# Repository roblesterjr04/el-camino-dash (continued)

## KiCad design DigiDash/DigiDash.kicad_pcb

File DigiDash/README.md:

# DigiDash main board, rev 1 (superseded)

**Status: superseded by [`DigiDash2/`](../DigiDash2/README.md).** Kept as the reference that rev 2 was planned from
([`docs/hardware/digidash_rev2_plan.md`](../docs/hardware/digidash_rev2_plan.md), "What rev 1 does badly"). Not on the
panel. Whether it was ever ordered or built: not stated.

**Firmware:** the on-board sensor pack runs [`arduino/sketches/sensor_pack`](../arduino/sketches/sensor_pack/); the
screens run [`firmware/esp32_p4_display`](../firmware/esp32_p4_display/).

The first main board: 309.2 × 103.7 mm, 2 layers, every part through-hole. On it:
- the three screen headers (2×20) for the Waveshare ESP32-P4 round displays, with an MCP2562 CAN transceiver per screen
- an **ATmega328P** (DIP-28) sensor pack whose serial output fans out to the three screens
  ([`docs/protocols/sensor_uart.md`](../docs/protocols/sensor_uart.md))
- plug-in modules: an FRAM board for the odometer and a TVP5150 video decoder board for the reversing camera
- an LM2576 5 V switching regulator
- four 2×5 accessory ports (J18–J21) and cable ports on the CAN bus
  ([`docs/hardware/accessory_ports.md`](../docs/hardware/accessory_ports.md), rev 1 sections)

| File | What |
| --- | --- |
| `DigiDash.kicad_sch` / `.kicad_pcb` / `.kicad_pro` | The board. There is no `generate/` folder; it was autorouted with Freerouting 2.1 (git history) |
| `DigiDash_Accessory.pretty` | The 2×5 accessory port and carrier header footprints. **Still in use:** DigiDash2, DigiDash3 and AudioCarrier list this library in their `fp-lib-table`, so keep the folder |
| `freerouting.dsn` | The Specctra export from the last autoroute |

The schematic uses symbols from KiCad's PCM SparkFun libraries (power symbols, a capacitor, a crystal) and an
`RCJ-022` symbol that is not in KiCad's stock libraries. Install those to open it without missing-symbol warnings.

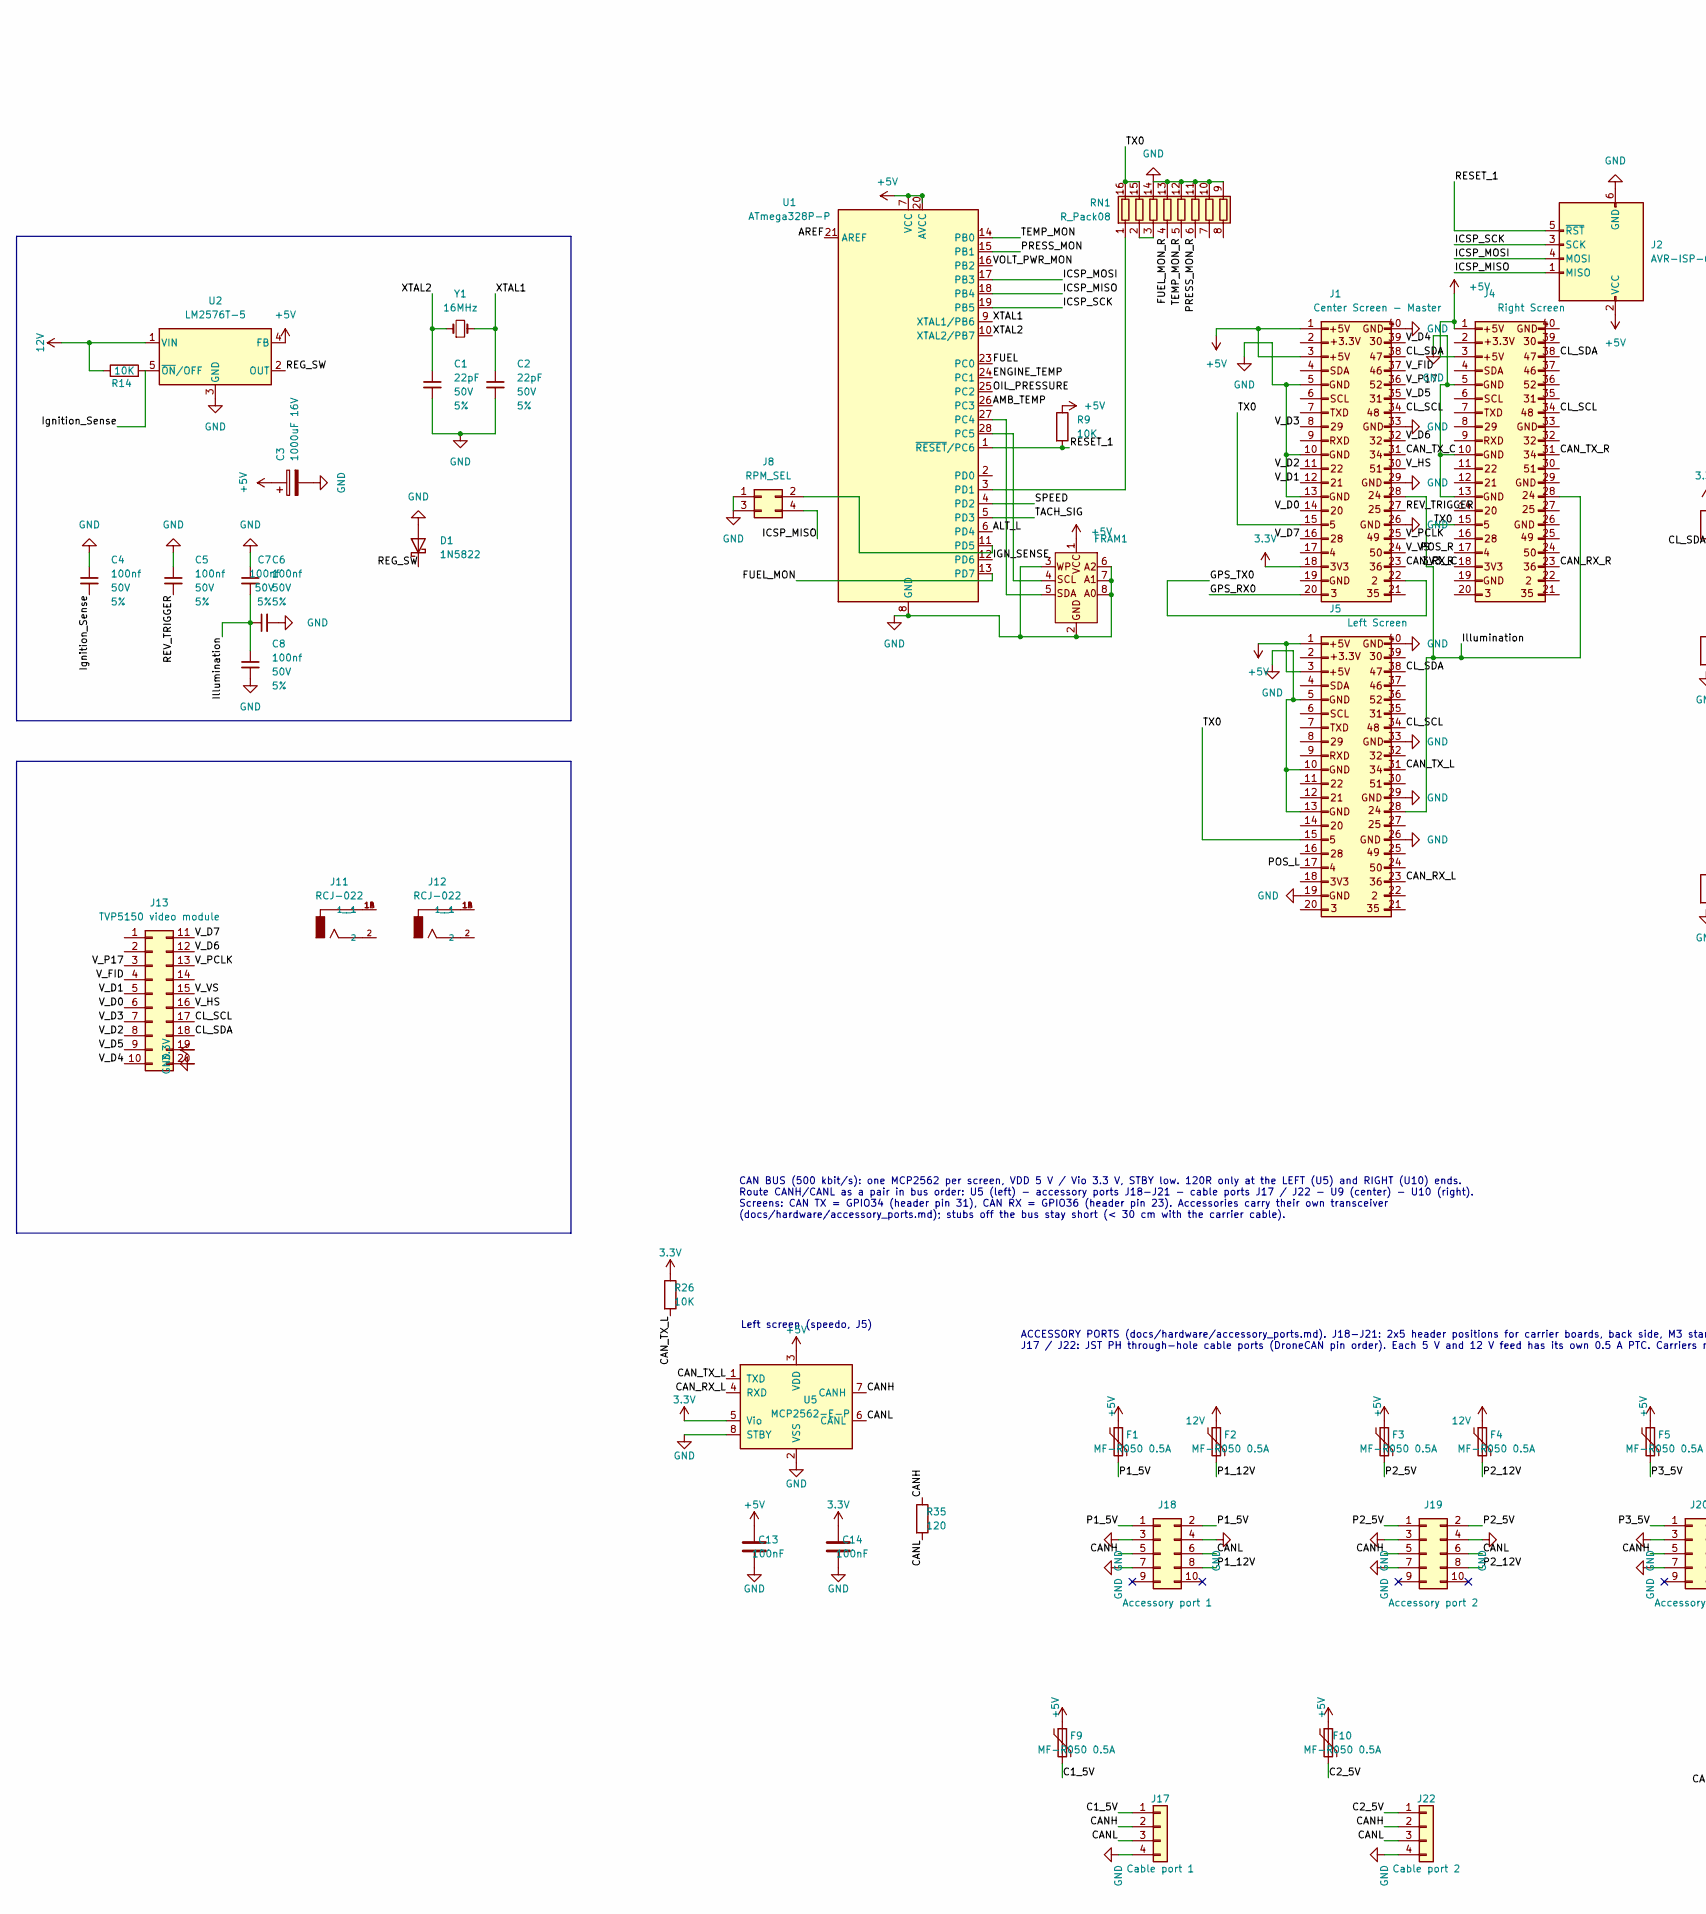
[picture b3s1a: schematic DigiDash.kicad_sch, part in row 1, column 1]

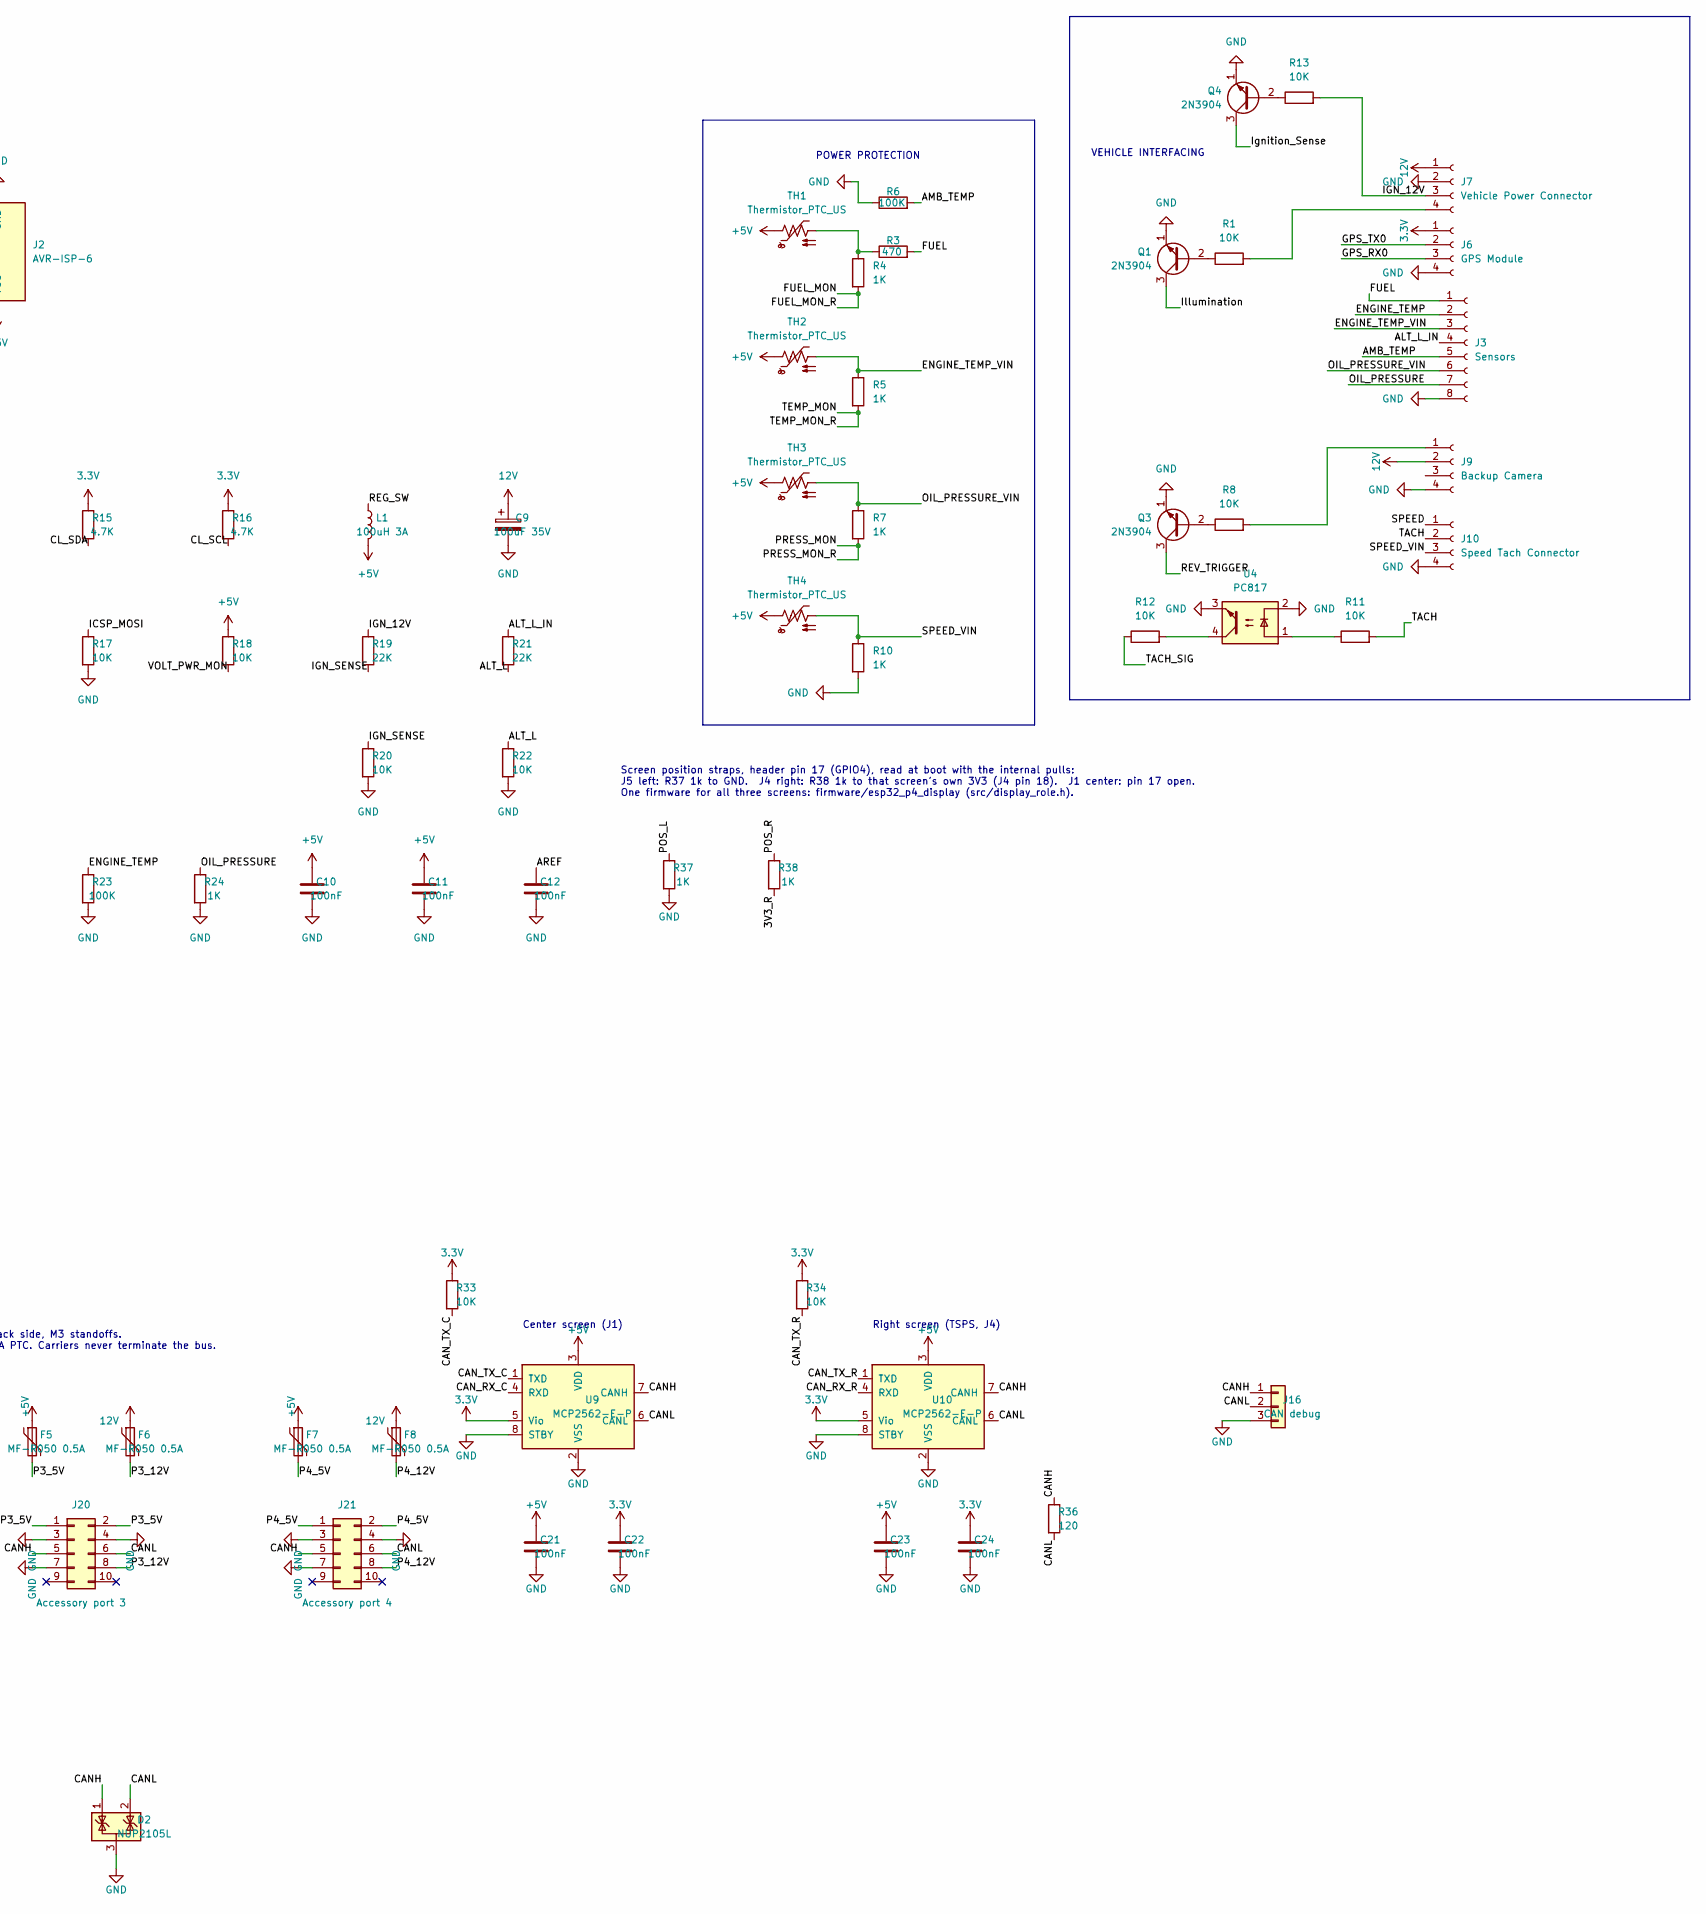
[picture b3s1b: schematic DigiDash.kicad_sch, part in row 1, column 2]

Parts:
C1, C2: 22pF; C_Disc_D3.0mm_W1.6mm_P2.50mm; Voltage 50V; Tolerance 5%
C3: 1000uF 16V; CP_Radial_D10.0mm_P5.00mm
C4, C5, C6, C7, C8: 100nf; C_Disc_D3.0mm_W1.6mm_P2.50mm; Voltage 50V; Tolerance 5%
C9: 100uF 35V; CP_Radial_D6.3mm_P2.50mm
C10, C11, C12, C13, C14, C21, C22, C23, C24: 100nF; C_Disc_D3.0mm_W1.6mm_P2.50mm
D1: 1N5822; D_DO-201AD_P15.24mm_Horizontal
D2: NUP2105L; SOT-23
F1, F2, F3, F4, F5, F6, F7, F8, F9, F10: MF-R050 0.5A; Fuse_Bourns_MF-RHT050
FRAM1: FRAM Board; PinHeader_1x08_P2.54mm_Vertical
J1: Center Screen - Master; PinHeader_2x20_P2.54mm_Vertical
J2: AVR-ISP-6; IDC-Header_2x03_P2.54mm_Vertical
J3: Sensors; JST_PH_S8B-PH-K_1x08_P2.00mm_Horizontal
J4: Right Screen; PinHeader_2x20_P2.54mm_Vertical
J5: Left Screen; PinHeader_2x20_P2.54mm_Vertical
J6: GPS Module; JST_PH_S4B-PH-K_1x04_P2.00mm_Horizontal
J7: Vehicle Power Connector; JST_PH_S4B-PH-K_1x04_P2.00mm_Horizontal
J8: RPM_SEL; PinHeader_2x02_P2.54mm_Vertical
J9: Backup Camera; JST_PH_S4B-PH-K_1x04_P2.00mm_Horizontal
J10: Speed Tach Connector; JST_PH_S4B-PH-K_1x04_P2.00mm_Horizontal
J11, J12: RCJ-022; CUI_RCJ-022; PART_REV B
J13: TVP5150 video module; PinSocket_2x10_P2.54mm_Vertical
J16: CAN debug; PinHeader_1x03_P2.54mm_Vertical
J17: Cable port 1; JST_PH_S4B-PH-K_1x04_P2.00mm_Horizontal
J18: Accessory port 1; Port_Header_2x05
J19: Accessory port 2; Port_Header_2x05
J20: Accessory port 3; Port_Header_2x05
J21: Accessory port 4; Port_Header_2x05
J22: Cable port 2; JST_PH_S4B-PH-K_1x04_P2.00mm_Horizontal
L1: 100uH 3A; L_Radial_D12.0mm_P10.00mm_Neosid_SD12_style1
Q1, Q3, Q4: 2N3904; TO-92_Inline
R1, R8, R9, R11, R12, R13, R14, R17, R18, R20, R22, R26, R33, R34: 10K; R_Axial_DIN0204_L3.6mm_D1.6mm_P5.08mm_Horizontal
R3: 470; R_Axial_DIN0204_L3.6mm_D1.6mm_P5.08mm_Horizontal
R4, R5, R7, R10, R24, R37, R38: 1K; R_Axial_DIN0204_L3.6mm_D1.6mm_P5.08mm_Horizontal
R6, R23: 100K; R_Axial_DIN0204_L3.6mm_D1.6mm_P5.08mm_Horizontal
R15, R16: 4.7K; R_Axial_DIN0204_L3.6mm_D1.6mm_P5.08mm_Horizontal
R19, R21: 22K; R_Axial_DIN0204_L3.6mm_D1.6mm_P5.08mm_Horizontal
R35, R36: 120; R_Axial_DIN0204_L3.6mm_D1.6mm_P5.08mm_Horizontal
RN1: R_Pack08; DIP-16_W7.62mm
TH1, TH2, TH3, TH4: Thermistor_PTC_US; R_Axial_DIN0516_L15.5mm_D5.0mm_P5.08mm_Vertical
U1: ATmega328P-P; DIP-28_W7.62mm
U2: LM2576T-5; TO-220-5_Vertical
U4: PC817; DIP-4_W7.62mm
U5, U9, U10: MCP2562-E-P; DIP-8_W7.62mm
Y1: 16MHz; Crystal_HC52-U_Vertical

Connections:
3.3V: C14.1, C22.1, C24.1, J1.18, J6.1, J13.19, R15.1, R16.1, R26.1, R33.1, R34.1, U5.5 (Vio), U9.5 (Vio), U10.5 (Vio)
12V: C9.1, F2.1, F4.1, F6.1, F8.1, J7.1, J9.2, R14.1, U2.1 (VIN)
+5V: C3.1, C10.1, C11.1, C13.1, C21.1, C23.1, F1.1, F3.1, F5.1, F7.1, F9.1, F10.1, FRAM1.1 (VCC), J1.1 (+5V), J1.3, J2.2 (VCC), J4.1 (+5V), J4.3, J5.1 (+5V), J5.3, L1.2, R9.1, R18.1, TH1.1, TH2.1, TH3.1, TH4.1, U1.7 (VCC), U1.20 (AVCC), U2.4 (FB), U5.3 (VDD), U9.3 (VDD), U10.3 (VDD)
/3V3_R: J4.18, R38.2
/ALT_L: R21.2, R22.1, U1.6 (PD4)
/ALT_L_IN: J3.4, R21.1
/AMB_TEMP: J3.5, R6.2, U1.26 (PC3)
/AREF: C12.1, U1.21 (AREF)
/C1_5V: F9.2, J17.1
/C2_5V: F10.2, J22.1
/CANH: D2.1 (K), J16.1, J17.2, J18.5, J19.5, J20.5, J21.5, J22.2, R35.1, R36.1, U5.7 (CANH), U9.7 (CANH), U10.7 (CANH)
/CANL: D2.2 (K), J16.2, J17.3, J18.6, J19.6, J20.6, J21.6, J22.3, R35.2, R36.2, U5.6 (CANL), U9.6 (CANL), U10.6 (CANL)
/CAN_RX_C: J1.23, U9.4 (RXD)
/CAN_RX_L: J5.23, U5.4 (RXD)
/CAN_RX_R: J4.23, U10.4 (RXD)
/CAN_TX_C: J1.31, R33.2, U9.1 (TXD)
/CAN_TX_L: J5.31, R26.2, U5.1 (TXD)
/CAN_TX_R: J4.31, R34.2, U10.1 (TXD)
/CL_SCL: J1.34, J4.34, J5.34, J13.17, R16.2
/CL_SDA: J1.38, J4.38, J5.38, J13.18, R15.2
/ENGINE_TEMP: J3.2, R23.1, U1.24 (PC1)
/ENGINE_TEMP_VIN: J3.3, R5.1, TH2.2
/FUEL: J3.1, R3.2, U1.23 (PC0)
/FUEL_MON: R4.2, RN1.4 (R4.1), U1.13 (PD7)
/GPS_RX0: J1.20, J6.3
/GPS_TX0: J1.22, J6.2
/ICSP_MISO: J2.1 (MISO), J8.4, U1.18 (PB4)
/ICSP_MOSI: J2.4 (MOSI), R17.1, U1.17 (PB3)
/ICSP_SCK: J2.3 (SCK), U1.19 (PB5)
/IGN_12V: J7.3, R13.2, R19.1
/IGN_SENSE: R19.2, R20.1, U1.12 (PD6)
/Ignition_Sense: C4.2, Q4.3 (C), R14.2, U2.5 (~ON/OFF)
/Illumination: C6.2, C7.1, C8.1, J1.28, J4.28, J5.28, Q1.3 (C)
/OIL_PRESSURE: J3.7, R24.1, U1.25 (PC2)
/OIL_PRESSURE_VIN: J3.6, R7.1, TH3.2
/P1_5V: F1.2, J18.1, J18.2
/P1_12V: F2.2, J18.8
/P2_5V: F3.2, J19.1, J19.2
/P2_12V: F4.2, J19.8
/P3_5V: F5.2, J20.1, J20.2
/P3_12V: F6.2, J20.8
/P4_5V: F7.2, J21.1, J21.2
/P4_12V: F8.2, J21.8
/POS_L: J5.17, R37.1
/POS_R: J4.17, R38.1
/PRESS_MON: R7.2, RN1.6 (R6.1), U1.15 (PB1)
/REG_SW: D1.1 (K), L1.1, U2.2 (OUT)
/RESET_1: J2.5 (~RST), R9.2, U1.1 (~RESET/PC6)
/REV_TRIGGER: C5.2, J1.27, Q3.3 (C)
/SPEED: J10.1, U1.4 (PD2)
/SPEED_VIN: J10.3, R10.1, TH4.2
/TACH: J10.2, R11.2
/TACH_SIG: R12.1, U1.5 (PD3)
/TEMP_MON: R5.2, RN1.5 (R5.1), U1.14 (PB0)
/TX0: J1.15, J4.15, J5.15, RN1.15 (R2.2), RN1.16 (R1.2)
/VOLT_PWR_MON: R18.2, U1.16 (PB2)
/V_D0: J1.14, J13.6
/V_D1: J1.12, J13.5
/V_D2: J1.11, J13.8
/V_D3: J1.8, J13.7
/V_D4: J1.39, J13.10
/V_D5: J1.35, J13.9
/V_D6: J1.32, J13.12
/V_D7: J1.16, J13.11
/V_FID: J1.37, J13.4
/V_HS: J1.30, J13.16
/V_P17: J1.36, J13.3
/V_PCLK: J1.25, J13.13
/V_VS: J1.24, J13.15
/XTAL1: C2.1, U1.9 (XTAL1/PB6), Y1.2
/XTAL2: C1.1, U1.10 (XTAL2/PB7), Y1.1
GND: C1.2, C2.2, C3.2, C4.1, C5.1, C6.1, C7.2, C8.2, C9.2, C10.2, C11.2, C12.2, C13.2, C14.2, C21.2, C22.2, C23.2, C24.2, D1.2 (A), D2.3 (A), FRAM1.2 (GND), FRAM1.3 (WP), FRAM1.6 (A2), FRAM1.7 (A1), FRAM1.8 (A2), J1.5, J1.10, J1.13 (GND), J1.26, J1.29, J1.33, J1.40, J2.6 (GND), J3.8, J4.5, J4.10, J4.13 (GND), J5.5, J5.10, J5.13 (GND), J5.19, J5.26, J5.29, J5.33, J5.40, J6.4, J7.2, J8.1, J8.3, J9.4, J10.4, J13.20, J16.3, J17.4, J18.3, J18.4, J18.7, J18.MP1, J18.MP2, J19.3, J19.4, J19.7, J19.MP1, J19.MP2, J20.3, J20.4, J20.7, J20.MP1, J20.MP2, J21.3, J21.4, J21.7, J21.MP1, J21.MP2, J22.4, Q1.1 (E), Q3.1 (E), Q4.1 (E), R6.1, R10.2, R17.2, R20.2, R22.2, R23.2, R24.2, R37.2, RN1.9 (R8.2), RN1.10 (R7.2), RN1.11 (R6.2), RN1.12 (R5.2), RN1.13 (R4.2), RN1.14 (R3.2), U1.8 (GND), U1.22 (GND), U2.3 (GND), U4.2, U4.3, U5.2 (VSS), U5.8 (STBY), U9.2 (VSS), U9.8 (STBY), U10.2 (VSS), U10.8 (STBY)
unnamed: FRAM1.4 (SCL), U1.28 (PC5)
unnamed: FRAM1.5 (SDA), U1.27 (PC4)
unnamed: J7.4, R1.2
unnamed: J8.2, U1.11 (PD5)
unnamed: J9.1, R8.2
unnamed: J11.1A (1), J11.1B (1__1)
unnamed: J12.1A (1), J12.1B (1__1)
unnamed: Q1.2 (B), R1.1
unnamed: Q3.2 (B), R8.1
unnamed: Q4.2 (B), R13.1
unnamed: R3.1, R4.1, TH1.2
unnamed: R11.1, U4.1
unnamed: R12.2, U4.4
unnamed: RN1.1 (R1.1), U1.3 (PD1)
unnamed: RN1.2 (R2.1), RN1.3 (R3.1)

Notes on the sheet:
VEHICLE INTERFACING
POWER PROTECTION
Left screen (speedo, J5)
Center screen (J1)
Right screen (TSPS, J4)
CAN BUS (500 kbit/s): one MCP2562 per screen, VDD 5 V / Vio 3.3 V, STBY low. 120R only at the LEFT (U5) and RIGHT (U10) ends. Route CANH/CANL as a pair in bus order: U5 (left) - accessory ports J18-J21 - cable ports J17 / J22 - U9 (center) - U10 (right). Screens: CAN TX = GPIO34 (header pin 31), CA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
Screen position straps, header pin 17 (GPIO4), read at boot with the internal pulls: J5 left: R37 1k to GND. J4 right: R38 1k to that screen's own 3V3 (J4 pin 18). J1 center: pin 17 open. One firmware for all three screens: firmware/esp32_p4_display (src/display_role.h).
ACCESSORY PORTS (docs/hardware/accessory_ports.md). J18-J21: 2x5 header positions for carrier boards, back side, M3 standoffs. J17 / J22: JST PH through-hole cable ports (DroneCAN pin order). Each 5 V and 12 V feed has its own 0.5 A PTC. Carriers never terminate the bus.

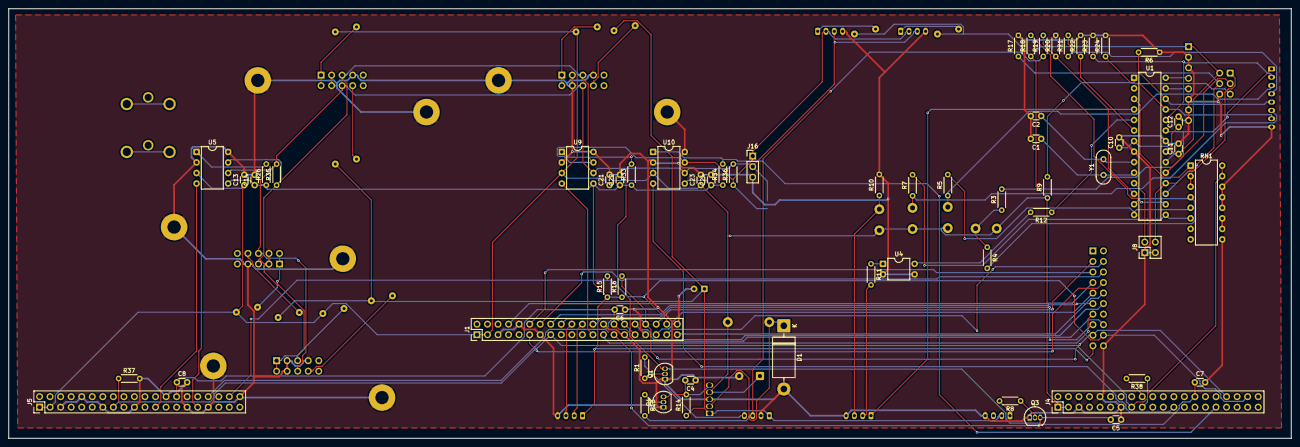
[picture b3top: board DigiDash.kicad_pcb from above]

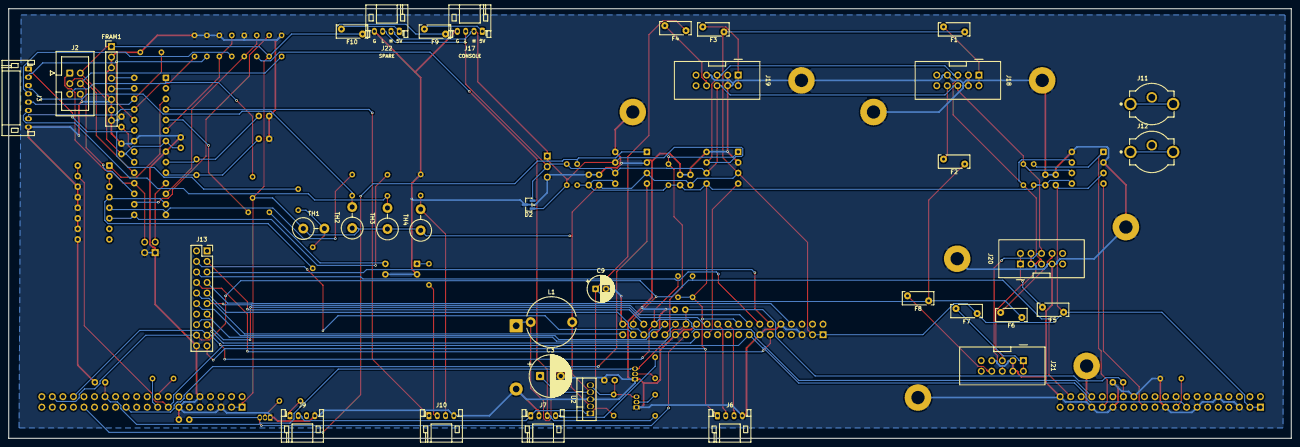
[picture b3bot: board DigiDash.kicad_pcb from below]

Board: 2 copper layers, 309.0 x 103.5 mm, 97 parts (35 on the bottom side), 87 nets.

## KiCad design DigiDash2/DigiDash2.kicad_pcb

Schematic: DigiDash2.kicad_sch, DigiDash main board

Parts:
C1, C18: 100u 63V; CP_Elec_10x10.5
C2, C3, C4, C5: 2.2u 100V; C_1210_3225Metric
C6, C7, C19, C20, C21, C22, C23, C24, C25, C26, C27, C28, C35, C36, C37, C38, C40, C41: 100n; C_0603_1608Metric
C8, C9, C10: 47u 10V; C_1210_3225Metric
C11: 4.7n; C_0603_1608Metric
C12: 47p; C_0603_1608Metric
C13, C14, C17, C39: 10u; C_0805_2012Metric
C15, C31, C32, C33: 1u; C_0603_1608Metric
C16: 4.7u; C_0805_2012Metric
C29, C30: 33p; C_0603_1608Metric
C34: 2.2u; C_0603_1608Metric
C42, C43: 220p; C_0603_1608Metric; not fitted
D2, D3: NUP2105L; SOT-23
D4, D8, D9: BZT52C15; D_SOD-123
D5, D10: SMCJ33A; D_SMC
D6: B560C; D_SMC
D7: BZT52C5V1; D_SOD-123
D11: PESD5V0S1BA; D_SOD-323
D12, D13, D14: BAT54S; SOT-23
F1: 5A mini blade; Fuseholder_Blade_Mini_Keystone_3568
F2, F3, F4, F5, F6, F8, F9, F12, F13, F16, F17, F20, F21, F24, F25, F28, F29: PTC 0.5A; Fuse_1812_4532Metric
F7: PTC 1.1A; Fuse_1812_4532Metric
F10, F14, F18, F22, F26, F30, F32: PTC 0.1A; Fuse_1206_3216Metric
F11, F15, F19, F23, F27, F31: PTC 0.2A; Fuse_1206_3216Metric
FB1: 600R; L_0603_1608Metric
H1, H2, H3, H4: MountingHole; MountingHole_3.2mm_M3_Pad
J1: Center Screen - Master; PinHeader_2x20_P2.54mm_Vertical
J4: Right Screen; PinHeader_2x20_P2.54mm_Vertical
J5: Left Screen; PinHeader_2x20_P2.54mm_Vertical
J6: Serial; JST_PH_B4B-PH-K_1x04_P2.00mm_Vertical
J7: Vehicle power; Molex_Micro-Fit_3.0_43650-0615_1x06_P3.00mm_Vertical
J9: Backup Camera; JST_PH_B4B-PH-K_1x04_P2.00mm_Vertical
J11: Video in; RCA_RCJ-02x_FaceMount
J13: AUX 12V in; Molex_Mini-Fit_Jr_5566-02A_2x01_P4.20mm_Vertical
J16: CAN debug; PinHeader_1x03_P2.54mm_Vertical
J17: Cable port 1; JST_PH_B4B-PH-K_1x04_P2.00mm_Vertical
J22: Cable port 2; JST_PH_B4B-PH-K_1x04_P2.00mm_Vertical
J23: Cable port 3; JST_PH_B4B-PH-K_1x04_P2.00mm_Vertical
J24: Cable port 4; JST_PH_B4B-PH-K_1x04_P2.00mm_Vertical
J25: Trunk port; Molex_Micro-Fit_3.0_43650-0415_1x04_P3.00mm_Vertical
J27: Sensor serial in; PinHeader_1x02_P2.54mm_Vertical
J31: Slot 1; Slot_Socket_2x15_P2.54mm_Vertical
J32: Slot 2; Slot_Socket_2x15_P2.54mm_Vertical
J33: Slot 3; Slot_Socket_2x15_P2.54mm_Vertical
J34: Slot 4; Slot_Socket_2x15_P2.54mm_Vertical
J35: Slot 5; Slot_Socket_2x15_P2.54mm_Vertical
J36: Slot 6; Slot_Socket_2x15_P2.54mm_Vertical
L1: 6.8u; L_Molded_1050
NT1, NT2: NetTie; NetTie-2_SMD_Pad2.0mm
Q1, Q3, Q4: MMBT3904; SOT-23
Q2, Q5, Q6: SUD50P04-08; TO-252-2
R1, R8, R11, R12, R15, R16, R17, R22, R23, R24, R25, R26, R28, R30, R36, R37, R38, R39: 10k; R_0603_1608Metric
R2: 243k; R_0603_1608Metric
R3: 53.6k; R_0603_1608Metric
R4: 10.2k; R_0603_1608Metric
R5: 16.9k; R_0603_1608Metric
R6: 442k; R_0603_1608Metric
R7: 90.9k; R_0603_1608Metric
R9, R20, R21: 4.7k; R_0603_1608Metric
R10, R45: 22k; R_0603_1608Metric
R13, R14, R40, R41: 1k; R_0603_1608Metric
R18, R19: 120; R_0603_1608Metric
R27, R29, R31: 20k; R_0603_1608Metric
R32, R33: 37.4; R_0603_1608Metric
R34: 22; R_0603_1608Metric
R35, R47, R49, R51: 100k; R_0603_1608Metric
R42: 3.3k; R_0603_1608Metric
R43: 6.8k; R_0603_1608Metric
R44: 12k; R_0603_1608Metric
R46, R48: 47k; R_0603_1608Metric
R50, R52: 27k; R_0603_1608Metric
R53: 0; R_0805_2012Metric
SW1: TERM; SW_DIP_SPSTx02_Slide_KingTek_DSHP02TS_W7.62mm_P1.27mm
U2: TPS54560BDDA; TI_SO-PowerPAD-8_ThermalVias
U5, U9, U10: TJA1051T/3; SOIC-8_3.9x4.9mm_P1.27mm
U8: TVP5150AM1IPBS; TQFP-32_5x5mm_P0.5mm
U11: AP7361C-33E; SOT-223-3_TabPin2
U12: AP2112K-1.8; SOT-23-5
Y3: 14.31818MHz; Crystal_SMD_3225-4Pin_3.2x2.5mm

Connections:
+3V3: C14.1, C15.1, C20.1, C22.1, C24.1, C38.1, D13.2 (K), D14.2 (K), F10.1, F14.1, F18.1, F22.1, F26.1, F30.1, F32.1, R15.1, R16.1, R17.1, R20.1, R21.1, R36.1, R39.1, U5.5 (Vio), U8.10 (IO_DVDD), U9.5 (Vio), U10.5 (Vio), U11.3 (VO), U12.1 (VIN), U12.3 (EN)
+5V: C8.1, C9.1, C10.1, C13.1, C19.1, C21.1, C23.1, F3.1, F4.1, F5.1, F6.1, F8.1, F12.1, F16.1, F20.1, F24.1, F28.1, J1.1, J1.3, J4.1, J4.3, J5.1, J5.3, L1.2, R3.1, U5.3 (VDD), U9.3 (VDD), U10.3 (VDD), U11.1 (VI)
/3V3_R: J4.18, R14.2
/12V_BATT: C1.1, C2.1, C3.1, C4.1, C5.1, C6.1, D4.1 (K), D5.1 (K), D8.1 (K), F11.1, F15.1, F19.1, F23.1, F27.1, F31.1, Q2.3 (S), Q5.3 (S), R8.1, U2.2 (VIN)
/+1V8: C16.1, C37.1, C39.1, FB1.1, U8.20 (DVDD), U12.5 (VOUT)
/+1V8A: C17.1, C35.1, C36.1, FB1.2, U8.4 (PLL_AVDD), U8.32 (CH_AVDD)
/AUDIO_GND: J31.23, J32.23, J33.23, J34.23, J35.23, J36.23, NT2.2 (B)
/AUDIO_L: J31.21, J32.21, J33.21, J34.21, J35.21, J36.21
/AUDIO_R: J31.22, J32.22, J33.22, J34.22, J35.22, J36.22
/AUX12: C18.1, D9.1 (K), D10.1 (K), J31.25, J31.26, J31.27, J32.25, J32.26, J32.27, J33.25, J33.26, J33.27, J34.25, J34.26, J34.27, J35.25, J35.26, J35.27, J36.25, J36.26, J36.27, Q6.3 (S)
/AUX_GND: C18.2, D10.2 (A), J13.2, J31.28, J31.29, J31.30, J32.28, J32.29, J32.30, J33.28, J33.29, J33.30, J34.28, J34.29, J34.30, J35.28, J35.29, J35.30, J36.28, J36.29, J36.30, NT1.2 (B), R12.2
/AUX_IN: F1.1, J13.1
/AUX_IN_F: F1.2, Q6.2 (D)
/BATT_IN: J7.1, J7.2, Q2.2 (D)
/BUCK_BOOT: C7.1, U2.1 (BOOT)
/BUCK_COMP: C12.1, R5.1, U2.6 (COMP)
/BUCK_CZ: C11.1, R5.2
/BUCK_EN: D7.1 (K), R6.2, R7.1, R48.2, U2.3 (EN)
/BUCK_FB: R3.2, R4.1, U2.5 (FB)
/BUCK_RT: R2.1, U2.4 (RT/CLK)
/BUCK_SW: C7.2, D6.1 (K), L1.1, U2.8 (SW)
/C1_5V: F3.2, J17.1
/C2_5V: F4.2, J22.1
/C3_5V: F5.2, J23.1
/C4_5V: F6.2, J24.1
/CAM_12V: F2.2, J9.2
/CANH: D2.1 (K), D3.1 (K), J16.1, J17.2, J22.2, J23.2, J24.2, J25.1, J31.5, J32.5, J33.5, J34.5, J35.5, J36.5, R18.1, R19.1, U5.7 (CANH), U9.7 (CANH), U10.7 (CANH)
/CANL: D2.2 (K), D3.2 (K), J16.2, J17.3, J22.3, J23.3, J24.3, J25.2, J31.6, J32.6, J33.6, J34.6, J35.6, J36.6, R18.2, SW1.4, U5.6 (CANL), U9.6 (CANL), U10.6 (CANL)
/CAN_RX_C: J1.23, U9.4 (RXD)
/CAN_RX_L: J5.23, U5.4 (RXD)
/CAN_RX_R: J4.23, U10.4 (RXD)
/CAN_TERM_R: R19.2, SW1.1
/CAN_TX_C: J1.31, R16.2, U9.1 (TXD)
/CAN_TX_L: J5.31, R15.2, U5.1 (TXD)
/CAN_TX_R: J4.31, R17.2, U10.1 (TXD)
/CL_SCL: J1.34, J4.34, J5.34, R21.2, U8.21 (SCL)
/CL_SDA: J1.38, J4.38, J5.38, R20.2, U8.22 (SDA)
/I2S_BCK: J31.15, J32.15, J33.15, J34.15, J35.15, J36.15
/I2S_MCLK: J31.24, J32.24, J33.24, J34.24, J35.24, J36.24
/I2S_MIC: J31.17, J32.17, J33.17, J34.17, J35.17, J36.17
/I2S_RET: J31.18, J32.18, J33.18, J34.18, J35.18, J36.18
/I2S_WS: J31.16, J32.16, J33.16, J34.16, J35.16, J36.16
/IGN_IN: J7.5, R6.1, R10.1
/ILLUM_IN: J7.6, R22.1, R49.1
/Illumination: C25.1, J1.28, Q1.3 (C)
/LAMP_LVL: C40.1, D13.3 (COM), J31.13, J32.13, J33.13, J34.13, J35.13, J36.13, R49.2, R50.1
/POS_L: J5.17, R13.1
/POS_R: J4.17, R14.1
/Q1_B: Q1.1 (B), R22.2, R23.1
/Q2_G: D4.2 (A), Q2.1 (G), R1.1
/Q3_B: Q3.1 (B), R24.2, R25.1
/Q4_B: Q4.1 (B), R10.2, R11.1
/Q4_C: Q4.3 (C), R9.2
/Q5_G: D8.2 (A), Q5.1 (G), R8.2, R9.1
/Q6_G: D9.2 (A), Q6.1 (G), R12.1
/REV_IN: J9.1, R24.1, R51.1
/REV_LVL: C41.1, D14.3 (COM), J31.14, J32.14, J33.14, J34.14, J35.14, J36.14, R51.2, R52.1
/REV_TRIGGER: C26.1, J1.27, Q3.3 (C)
/S1_3V3: F10.2, J31.9
/S1_5V: F8.2, J31.1, J31.2
/S1_12V: F9.2, J31.8
/S1_BATT: F11.2, J31.10
/S1_ID: J31.11, R41.1
/S2_3V3: F14.2, J32.9
/S2_5V: F12.2, J32.1, J32.2
/S2_12V: F13.2, J32.8
/S2_BATT: F15.2, J32.10
/S2_ID: J32.11, R42.1
/S3_3V3: F18.2, J33.9
/S3_5V: F16.2, J33.1, J33.2
/S3_12V: F17.2, J33.8
/S3_BATT: F19.2, J33.10
/S3_ID: J33.11, R43.1
/S4_3V3: F22.2, J34.9
/S4_5V: F20.2, J34.1, J34.2
/S4_12V: F21.2, J34.8
/S4_BATT: F23.2, J34.10
/S4_ID: J34.11, R44.1
/S5_3V3: F26.2, J35.9
/S5_5V: F24.2, J35.1, J35.2
/S5_12V: F25.2, J35.8
/S5_BATT: F27.2, J35.10
/S5_ID: J35.11, R45.1
/S6_3V3: F30.2, J36.9
/S6_5V: F28.2, J36.1, J36.2
/S6_12V: F29.2, J36.8
/S6_BATT: F31.2, J36.10
/S6_ID: J36.11, R46.1
/SENS_TX: J27.1, R26.1, R28.1, R30.1
/SENS_TX_C: J1.15, R28.2, R29.1
/SENS_TX_L: J5.15, R26.2, R27.1
/SENS_TX_R: J4.15, R30.2, R31.1
/SER_3V3: F32.2, J6.1
/SER_RX: J1.20, J6.3
/SER_TX: J1.22, J6.2
/SW12: F2.1, F7.1, F9.1, F13.1, F17.1, F21.1, F25.1, F29.1, Q5.2 (D)
/TRUNK_12V: F7.2, J25.3
/VIDEO_IN: C42.1, D11.1 (K), J11.1 (In), R53.1
/VID_AAF: C43.1, R32.1, R53.2
/VID_AIP1A: C27.2, U8.1 (AIP1A)
/VID_AIP1B: C28.1, U8.2 (AIP1B)
/VID_ATT: C27.1, R32.2, R33.1
/VID_INTREQ: R37.1, U8.27 (INTREQ/GPCL/VBLK)
/VID_PDN: R36.2, U8.28 (PDN)
/VID_REFM: C32.1, C33.2, U8.30 (REFM)
/VID_REFP: C31.1, C33.1, U8.29 (REFP)
/VID_RESETB: C34.1, R39.2, R40.2, U8.8 (RESETB)
/VID_SCLK: R34.1, U8.9 (SCLK)
/VID_XTAL1: C29.1, R35.1, U8.5 (XTAL1/OSC), Y3.1
/VID_XTAL2: C30.1, R35.2, U8.6 (XTAL2), Y3.3
/V_D0: J1.14, U8.18 (YOUT0)
/V_D1: J1.12, U8.17 (YOUT1)
/V_D2: J1.11, U8.16 (YOUT2)
/V_D3: J1.8, U8.15 (YOUT3)
/V_D4: J1.39, U8.14 (YOUT4)
/V_D5: J1.35, U8.13 (YOUT5)
/V_D6: J1.32, U8.12 (YOUT6)
/V_D7: J1.16, R38.1, U8.11 (YOUT7/I2CSEL)
/V_FID: J1.37, U8.23 (FID/GLCO)
/V_HS: J1.30, U8.25 (HSYNC)
/V_P17: J1.36, R40.1
/V_PCLK: J1.25, R34.2
/V_VS: J1.24, U8.24 (VSYNC/PALI)
/WAKE: D12.1 (A), J31.12, J32.12, J33.12, J34.12, J35.12, J36.12, R47.1
/WAKE_K: D12.3 (COM), R48.1
GND: C1.2, C2.2, C3.2, C4.2, C5.2, C6.2, C8.2, C9.2, C10.2, C11.2, C12.2, C13.2, C14.2, C15.2, C16.2, C17.2, C19.2, C20.2, C21.2, C22.2, C23.2, C24.2, C25.2, C26.2, C28.2, C29.2, C30.2, C31.2, C32.2, C34.2, C35.2, C36.2, C37.2, C38.2, C39.2, C40.2, C41.2, C42.2, C43.2, D2.3 (A), D3.3 (A), D5.2 (A), D6.2 (A), D7.2 (A), D11.2 (A), D13.1 (A), D14.1 (A), H1.1, H2.1, H3.1, H4.1, J1.5, J1.10, J1.13, J1.26, J1.29, J1.33, J1.40, J4.5, J4.10, J4.13, J5.5, J5.10, J5.13, J5.19, J5.26, J5.29, J5.33, J5.40, J6.4, J7.3, J7.4, J9.4, J11.2 (Ext), J16.3, J17.4, J22.4, J23.4, J24.4, J25.4, J27.2, J31.3, J31.4, J31.7, J31.19, J31.20, J32.3, J32.4, J32.7, J32.19, J32.20, J33.3, J33.4, J33.7, J33.19, J33.20, J34.3, J34.4, J34.7, J34.19, J34.20, J35.3, J35.4, J35.7, J35.19, J35.20, J36.3, J36.4, J36.7, J36.19, J36.20, NT1.1 (A), NT2.1 (A), Q1.2 (E), Q3.2 (E), Q4.2 (E), R1.2, R2.2, R4.2, R7.2, R11.2, R13.2, R23.2, R25.2, R27.2, R29.2, R31.2, R33.2, R37.2, R38.2, R41.2, R42.2, R43.2, R44.2, R45.2, R46.2, R47.2, R50.2, R52.2, U2.7 (GND), U2.9 (GND), U5.2 (VSS), U5.8 (STBY), U8.3 (PLL_AGND), U8.7 (AGND), U8.19 (DGND), U8.31 (CH_AGND), U9.2 (VSS), U9.8 (STBY), U10.2 (VSS), U10.8 (STBY), U11.2 (GND), U12.2 (GND), Y3.2 (G), Y3.4 (G)

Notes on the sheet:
DIGIDASH MAIN BOARD, REV 2 - docs/hardware/digidash_rev2_plan.md
All SMD except connectors. The sensor pack is a slot card (SensorCard/, CAN node 0x04); J27 takes its optional sensor-frame serial line (a jumper wire) and fans it out to the three screens. TVP5150AM1 on the board. Six 2x15 card slots (cards stand on edge), four cable ports, a trunk port, and an AU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
POWER: J7 (battery, ignition, illumination), reverse protection, TVS, 5 A buck (TI TPS54560B typical application, 400 kHz), 3.3 V and 1.8 V LDOs, switched 12 V
EN: the 5 V rail runs while the ignition is on, or while a card holds WAKE high (the sensor card does, to finish after key-off). IGN 12 V -> 442k / 90.9k (starts above ~6.5 V), clamped by a 5.1 V zener (EN abs. max 8.4 V). WAKE -> BAT54S -> 47k also lifts EN (slots block).
SW12 (switched 12 V for the slots' pin 8, the trunk port and the camera): a P-FET high-side switch from 12V_BATT, on while the ignition is on.
AUX 12 V: slot power from its own fused feed (pins 25-30 of every slot). Its return (AUX_GND) meets GND only at NT1.
SCREENS: J5 left, J1 center, J4 right (ESP32-P4, plugged in face down). One MCP2562 each (VIO from the board 3.3 V). 120 R at the left (R) and right (bridged jumper) ends of the bus.
Vehicle inputs to the screens (as rev 1): illumination (J7 pin 6), reverse (J9 pin 1). J6: serial port (center UART2).
Sensor serial (optional, a jumper wire from the sensor card): J27 pin 1 (5 V TX) -> 10k / 20k divider per screen (5 V -> 3.3 V) -> pin 15 of J5 / J1 / J4. Sensor data normally arrives on CAN; this is the fallback path.
VIDEO: composite (J11) -> TVP5150AM1 -> 8-bit BT.656 to the center's camera pins, same J1 pins as rev 1's module. I2C on the cluster bus, address 0x5C (YOUT7 pulled down). TI SLES209E figure 6-1.
CABLE PORTS J17, J22, J23, J24 (JST PH). Trunk port J25 (bus extension, 12 V).
SLOTS: six 2x15 sockets J31-J36 (slot 1-6), cards stand on edge (docs/hardware/accessory_ports.md). Per slot: fused 5 V, switched 12 V, 3.3 V, constant 12 V, an ID resistor. Shared: CAN, WAKE, LAMP / REV levels, the analog audio bus, AUX 12 V, and the I2S rail (BCK, WS, MIC, RET, MCLK: bused to all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
WAKE: a card drives it high (about 3.3 V, through its own diode) to start or hold the 5 V rail with the key off (the sensor card holds it to finish after key-off). LAMP_LVL / REV_LVL: J7 pin 6 and J9 pin 1 scaled to 0-3.3 V.
